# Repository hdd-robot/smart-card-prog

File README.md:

# smart-card-prog
Smart card programer and smart card with ATMEGA 328

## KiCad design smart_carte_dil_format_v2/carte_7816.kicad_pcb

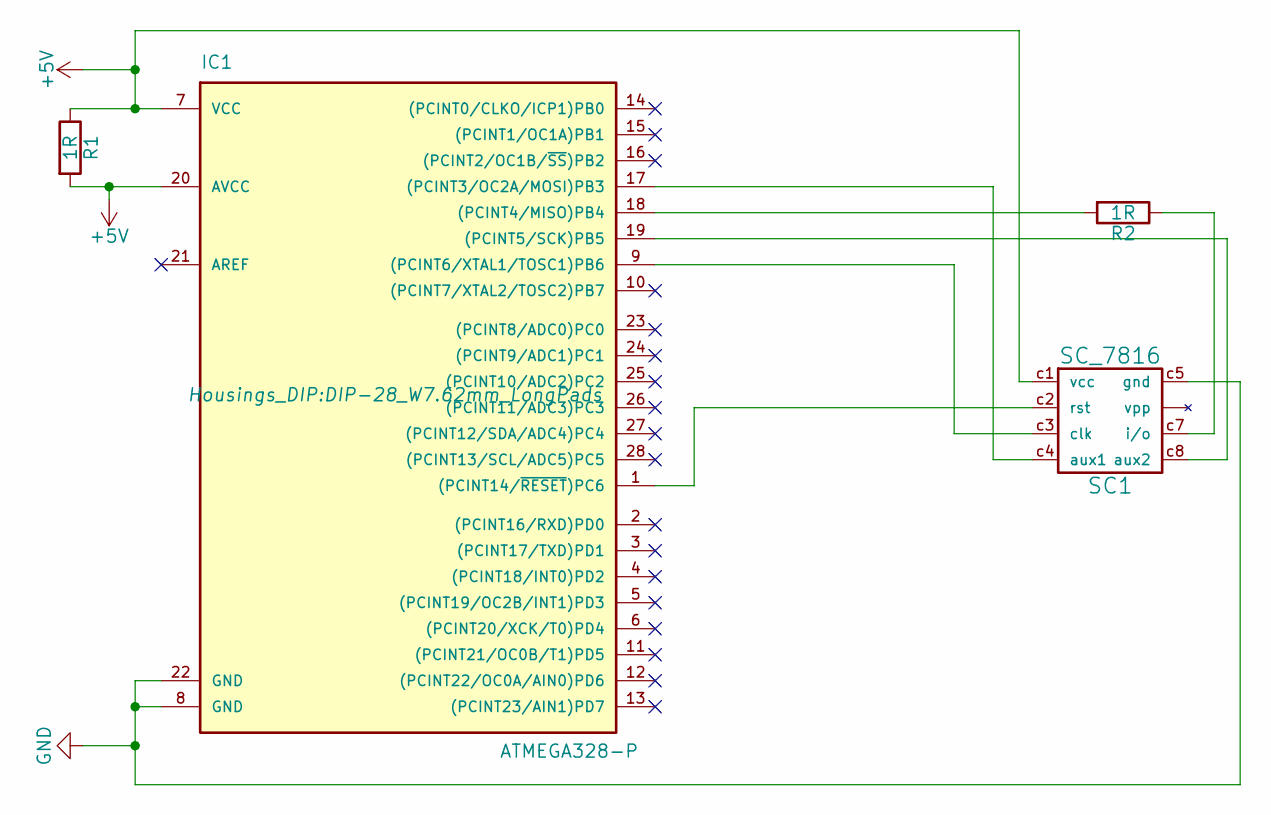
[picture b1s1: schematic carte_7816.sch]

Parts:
IC1: ATMEGA328-P; DIP-28_W7.62mm_LongPads
R1, R2: 1R; Resistor_Horizontal_RM15mm
SC1: SC_7816; card_connector_iso7816

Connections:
+5V: IC1.7 (VCC), IC1.20 (AVCC), R1.1, R1.2, SC1.c1 (vcc)
GND: IC1.8 (GND), IC1.22 (GND), SC1.c5 (gnd)
unnamed: IC1.1 ((PCINT14/~RESET~)PC6), SC1.c2 (rst)
unnamed: IC1.9 ((PCINT6/XTAL1/TOSC1)PB6), SC1.c3 (clk)
unnamed: IC1.17 ((PCINT3/OC2A/MOSI)PB3), SC1.c4 (aux1)
unnamed: IC1.18 ((PCINT4/MISO)PB4), R2.2
unnamed: IC1.19 ((PCINT5/SCK)PB5), SC1.c8 (aux2)
unnamed: R2.1, SC1.c7 (i/o)

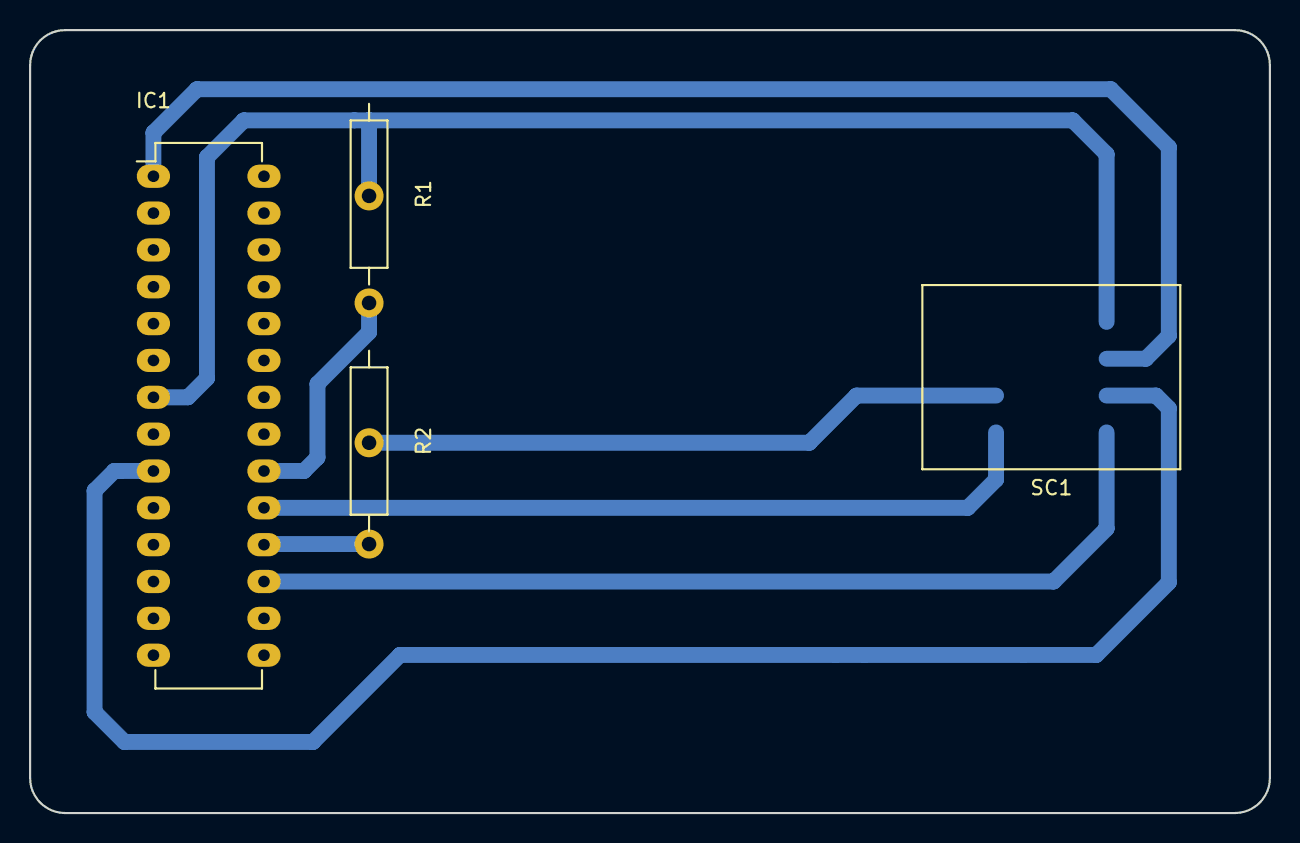
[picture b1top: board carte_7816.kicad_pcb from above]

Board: 2 copper layers, 85.5 x 54.0 mm, 4 parts (0 on the bottom side), 8 nets.

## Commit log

2021-11-15 3D print Box for programmer
2021-11-15 Smart card TQFP Format
2021-11-15 Smart_card_dil_format_v1
2021-11-15 Smart_card_dil_format_v2
2021-11-15 Smart_card_dil_format_v3
2021-11-15 Smart card lib for KICAD
2021-11-15 Hello world programe
2021-11-15 add images
